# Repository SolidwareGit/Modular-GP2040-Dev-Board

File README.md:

# Modular-GP2040-Dev-Board
This is a development board for the RP2040 to enable creation of a modular GP2040-CE, using I2C, for fightsticks or other controller peripherals

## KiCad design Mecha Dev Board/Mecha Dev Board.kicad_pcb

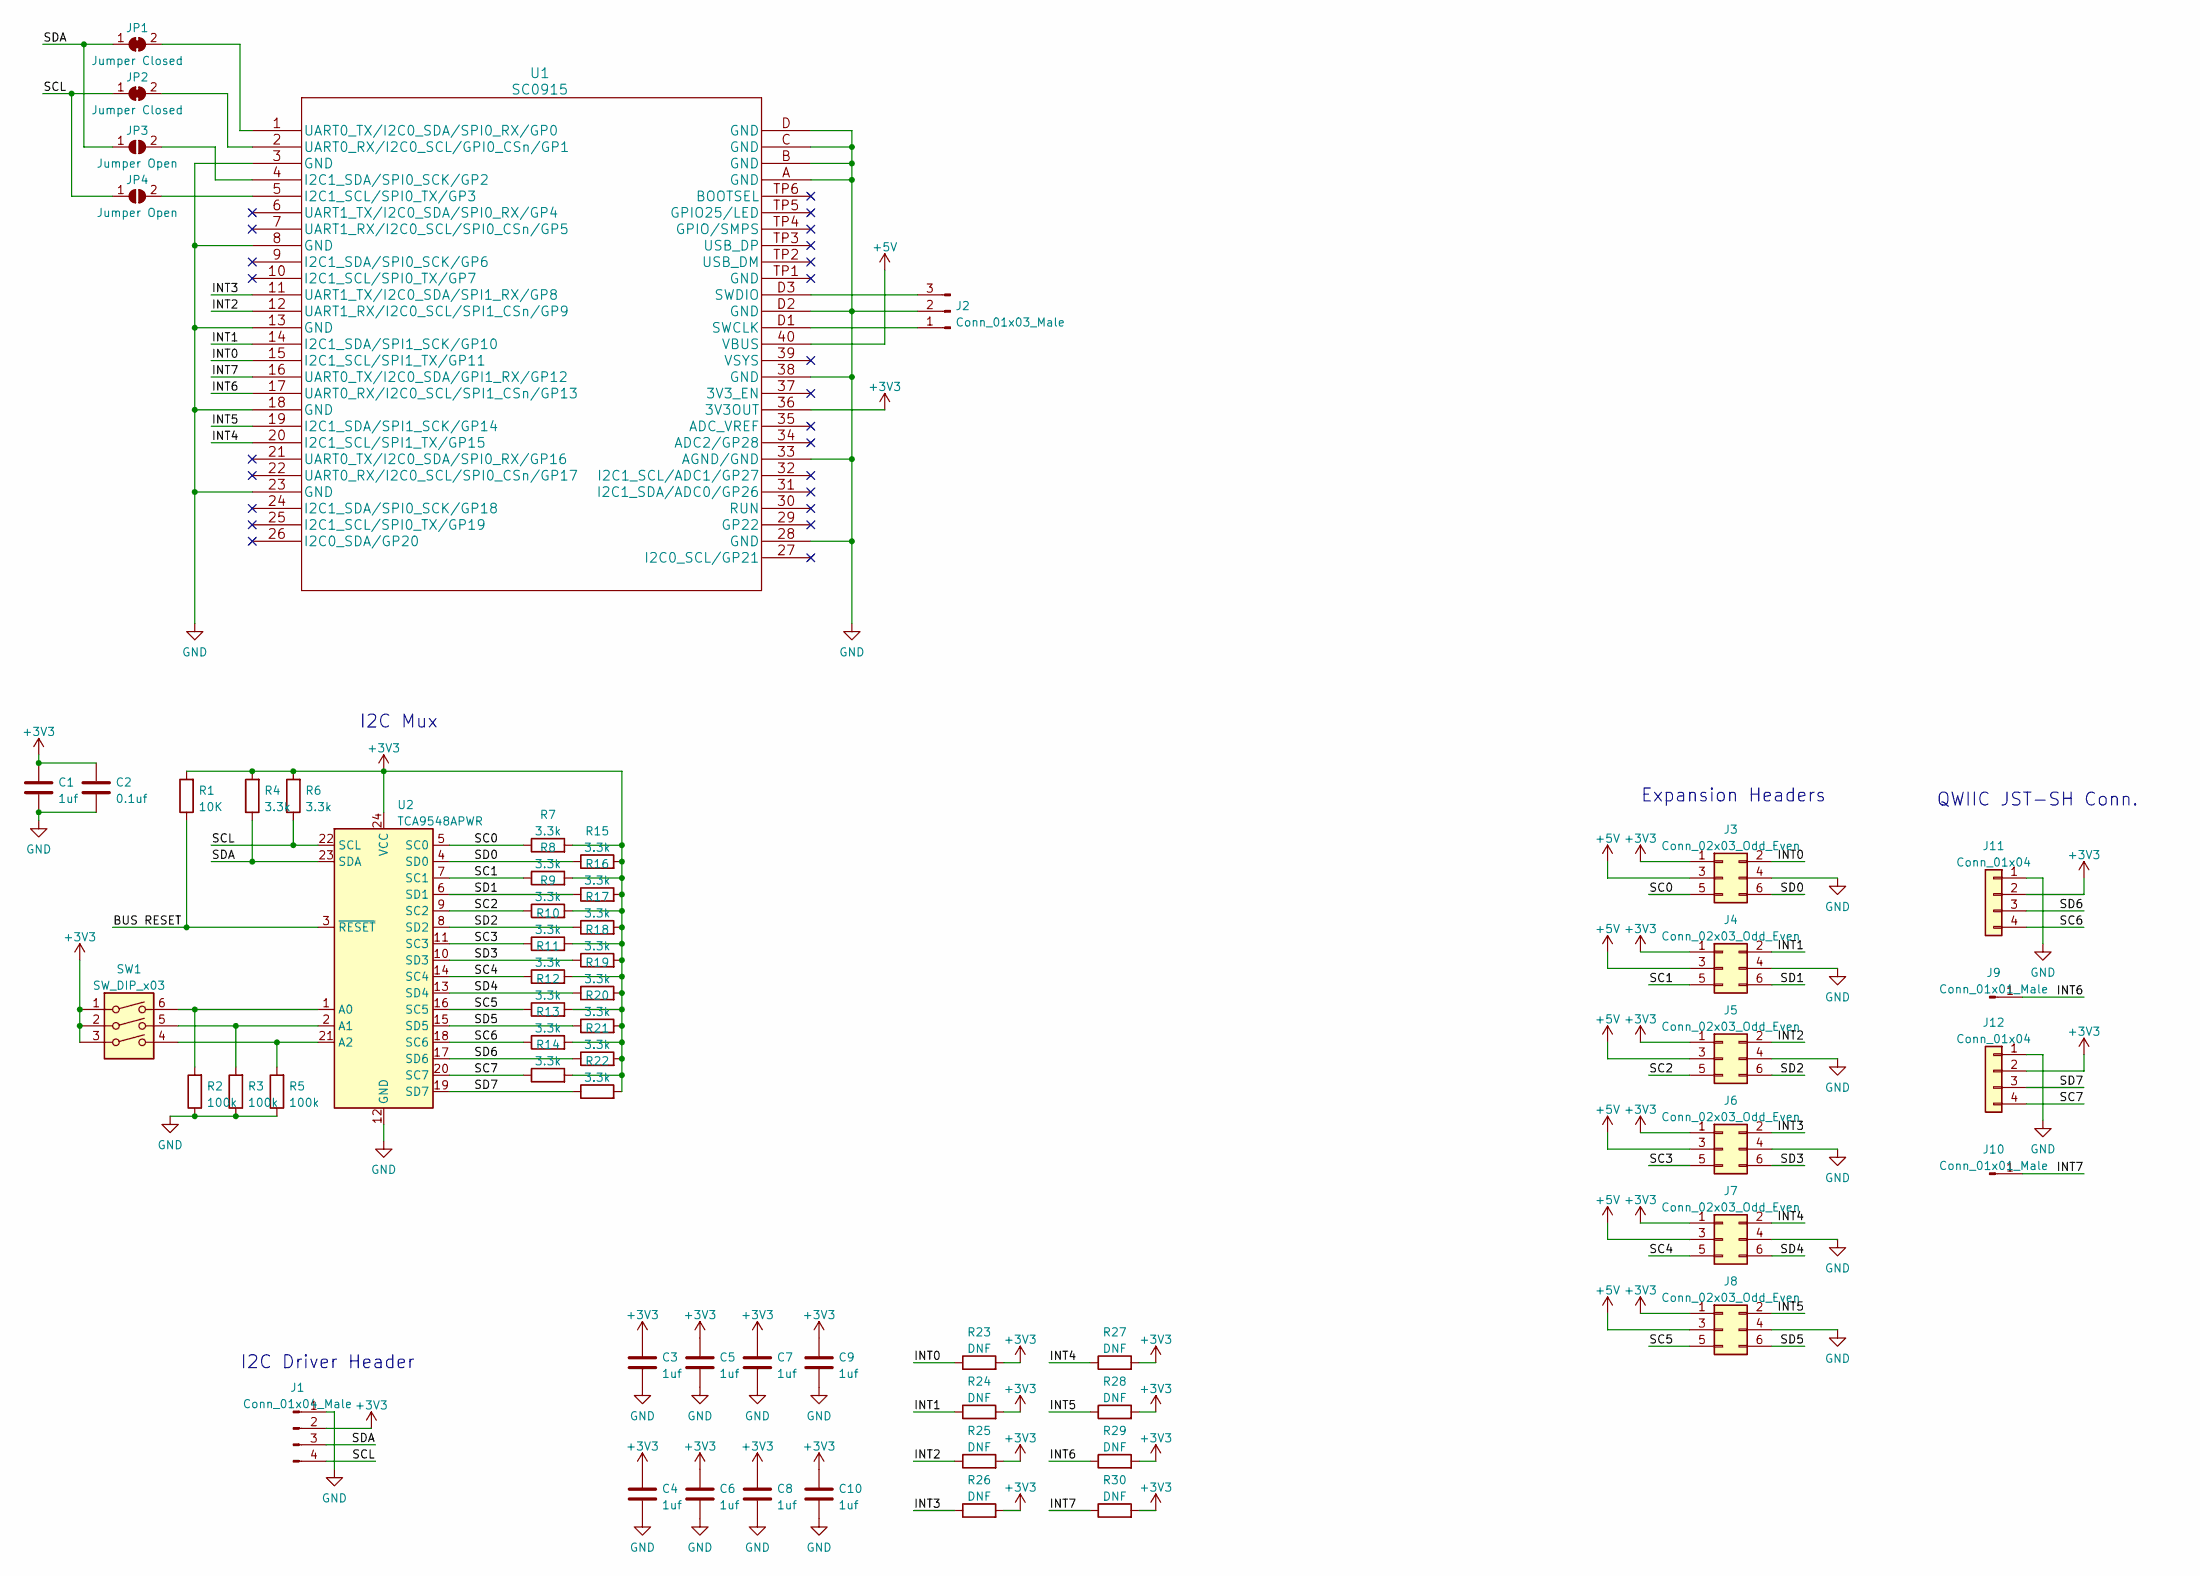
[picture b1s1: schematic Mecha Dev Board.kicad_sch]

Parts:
C1, C3, C4, C5, C6, C7, C8, C9, C10: 1uf; C_0805_2012Metric_Pad1.18x1.45mm_HandSolder
C2: 0.1uf; C_0805_2012Metric_Pad1.18x1.45mm_HandSolder
J1: Conn_01x04_Male; PinHeader_1x04_P2.54mm_Vertical
J2: Conn_01x03_Male; PinHeader_1x03_P2.54mm_Vertical
J3, J4, J5, J6, J7, J8: Conn_02x03_Odd_Even; PinHeader_2x03_P2.54mm_Vertical
J9, J10: Conn_01x01_Male; PinHeader_1x01_P2.54mm_Vertical
J11, J12: Conn_01x04; JST_SH_SM04B-SRSS-TB_1x04-1MP_P1.00mm_Horizontal
JP1, JP2: Jumper Closed; SolderJumper-2_P1.3mm_Bridged_Pad1.0x1.5mm
JP3, JP4: Jumper Open; SolderJumper-2_P1.3mm_Open_Pad1.0x1.5mm
R1: 10K; R_0805_2012Metric_Pad1.20x1.40mm_HandSolder
R2, R3, R5: 100k; R_0805_2012Metric_Pad1.20x1.40mm_HandSolder
R4, R6, R7, R8, R9, R10, R11, R12, R13, R14, R15, R16, R17, R18, R19, R20, R21, R22: 3.3k; R_0805_2012Metric_Pad1.20x1.40mm_HandSolder
R23, R24, R25, R26, R27, R28, R29, R30: DNF; R_0805_2012Metric_Pad1.20x1.40mm_HandSolder
SW1: SW_DIP_x03; SW_DIP_SPSTx03_Slide_6.7x9.18mm_W7.62mm_P2.54mm_LowProfile
U1: SC0915
U2: TCA9548APWR; TSSOP-24_4.4x7.8mm_P0.65mm

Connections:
+3V3: C1.2, C2.2, C3.2, C4.2, C5.2, C6.2, C7.2, C8.2, C9.2, C10.2, J1.2, J3.1, J4.1, J5.1, J6.1, J7.1, J8.1, J11.2, J12.2, R1.2, R4.2, R6.2, R7.2, R8.2, R9.2, R10.2, R11.2, R12.2, R13.2, R14.2, R15.2, R16.2, R17.2, R18.2, R19.2, R20.2, R21.2, R22.2, R23.2, R24.2, R25.2, R26.2, R27.2, R28.2, R29.2, R30.2, SW1.1, SW1.2, SW1.3, U1.36 (3V3OUT), U2.24 (VCC)
+5V: J3.3, J4.3, J5.3, J6.3, J7.3, J8.3, U1.40 (VBUS)
/BUS RESET: R1.1, U2.3 (~RESET)
/INT0: J3.2, R23.1, U1.15 (I2C1_SCL/SPI1_TX/GP11)
/INT1: J4.2, R24.1, U1.14 (I2C1_SDA/SPI1_SCK/GP10)
/INT2: J5.2, R25.1, U1.12 (UART1_RX/I2C0_SCL/SPI1_CSn/GP9)
/INT3: J6.2, R26.1, U1.11 (UART1_TX/I2C0_SDA/SPI1_RX/GP8)
/INT4: J7.2, R27.1, U1.20 (I2C1_SCL/SPI1_TX/GP15)
/INT5: J8.2, R28.1, U1.19 (I2C1_SDA/SPI1_SCK/GP14)
/INT6: J9.1, R29.1, U1.17 (UART0_RX/I2C0_SCL/SPI1_CSn/GP13)
/INT7: J10.1, R30.1, U1.16 (UART0_TX/I2C0_SDA/GPI1_RX/GP12)
/SC0: J3.5, R7.1, U2.5 (SC0)
/SC1: J4.5, R8.1, U2.7 (SC1)
/SC2: J5.5, R9.1, U2.9 (SC2)
/SC3: J6.5, R10.1, U2.11 (SC3)
/SC4: J7.5, R11.1, U2.14 (SC4)
/SC5: J8.5, R12.1, U2.16 (SC5)
/SC6: J11.4, R13.1, U2.18 (SC6)
/SC7: J12.4, R14.1, U2.20 (SC7)
/SCL: J1.4, JP2.1 (A), JP4.1 (A), R6.1, U2.22 (SCL)
/SD0: J3.6, R15.1, U2.4 (SD0)
/SD1: J4.6, R16.1, U2.6 (SD1)
/SD2: J5.6, R17.1, U2.8 (SD2)
/SD3: J6.6, R18.1, U2.10 (SD3)
/SD4: J7.6, R19.1, U2.13 (SD4)
/SD5: J8.6, R20.1, U2.15 (SD5)
/SD6: J11.3, R21.1, U2.17 (SD6)
/SD7: J12.3, R22.1, U2.19 (SD7)
/SDA: J1.3, JP1.1 (A), JP3.1 (A), R4.1, U2.23 (SDA)
GND: C1.1, C2.1, C3.1, C4.1, C5.1, C6.1, C7.1, C8.1, C9.1, C10.1, J1.1, J2.2, J3.4, J4.4, J5.4, J6.4, J7.4, J8.4, J11.1, J12.1, R2.1, R3.1, R5.1, U1.3 (GND), U1.8 (GND), U1.13 (GND), U1.18 (GND), U1.23 (GND), U1.28 (GND), U1.33 (AGND/GND), U1.38 (GND), U1.A (GND), U1.B (GND), U1.C (GND), U1.D (GND), U1.D2 (GND), U2.12 (GND)
unnamed: J2.1, U1.D1 (SWCLK)
unnamed: J2.3, U1.D3 (SWDIO)
unnamed: JP1.2 (B), U1.1 (UART0_TX/I2C0_SDA/SPI0_RX/GP0)
unnamed: JP2.2 (B), U1.2 (UART0_RX/I2C0_SCL/GPI0_CSn/GP1)
unnamed: JP3.2 (B), U1.4 (I2C1_SDA/SPI0_SCK/GP2)
unnamed: JP4.2 (B), U1.5 (I2C1_SCL/SPI0_TX/GP3)
unnamed: R2.2, SW1.6, U2.1 (A0)
unnamed: R3.2, SW1.5, U2.2 (A1)
unnamed: R5.2, SW1.4, U2.21 (A2)

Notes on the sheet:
I2C Driver Header
I2C Mux
Expansion Headers
QWIIC JST-SH Conn.

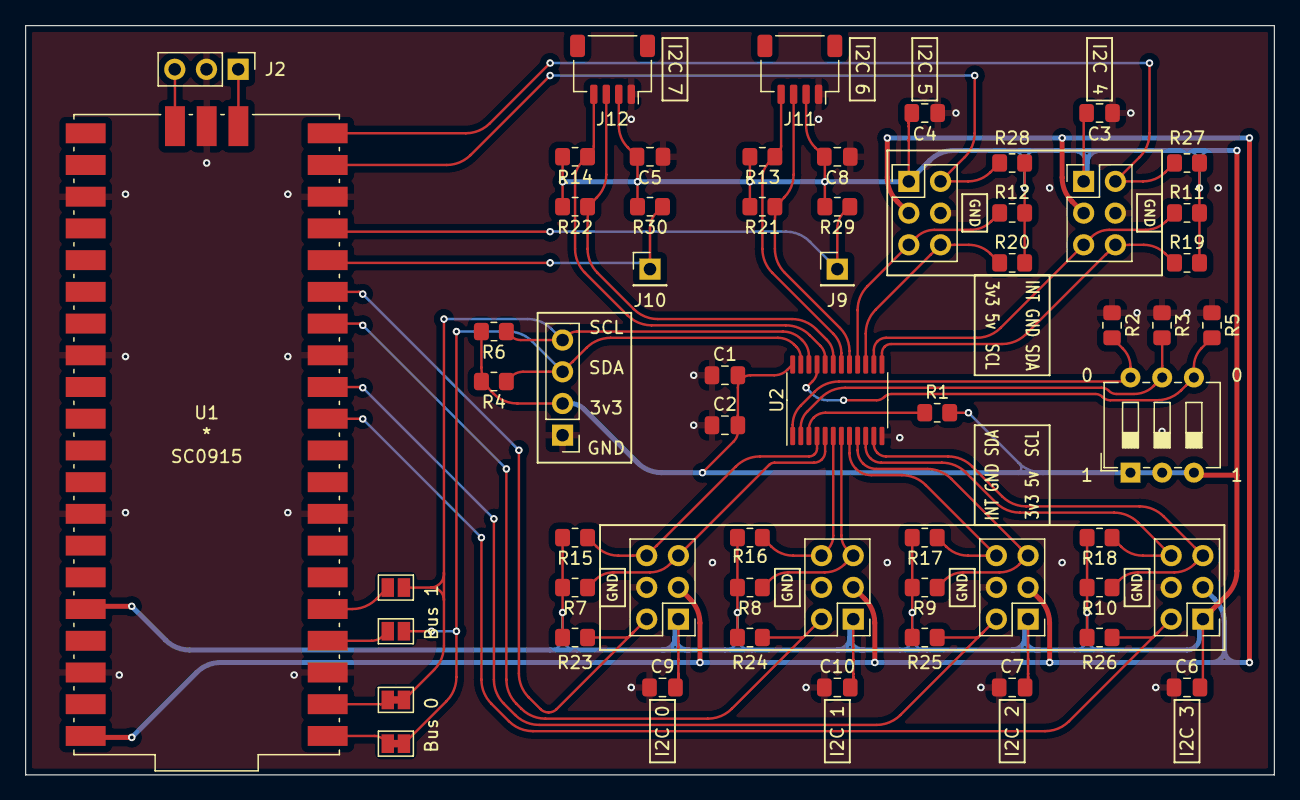
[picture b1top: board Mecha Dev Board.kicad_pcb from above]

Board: 2 copper layers, 100.0 x 60.0 mm, 59 parts (0 on the bottom side), 39 nets.

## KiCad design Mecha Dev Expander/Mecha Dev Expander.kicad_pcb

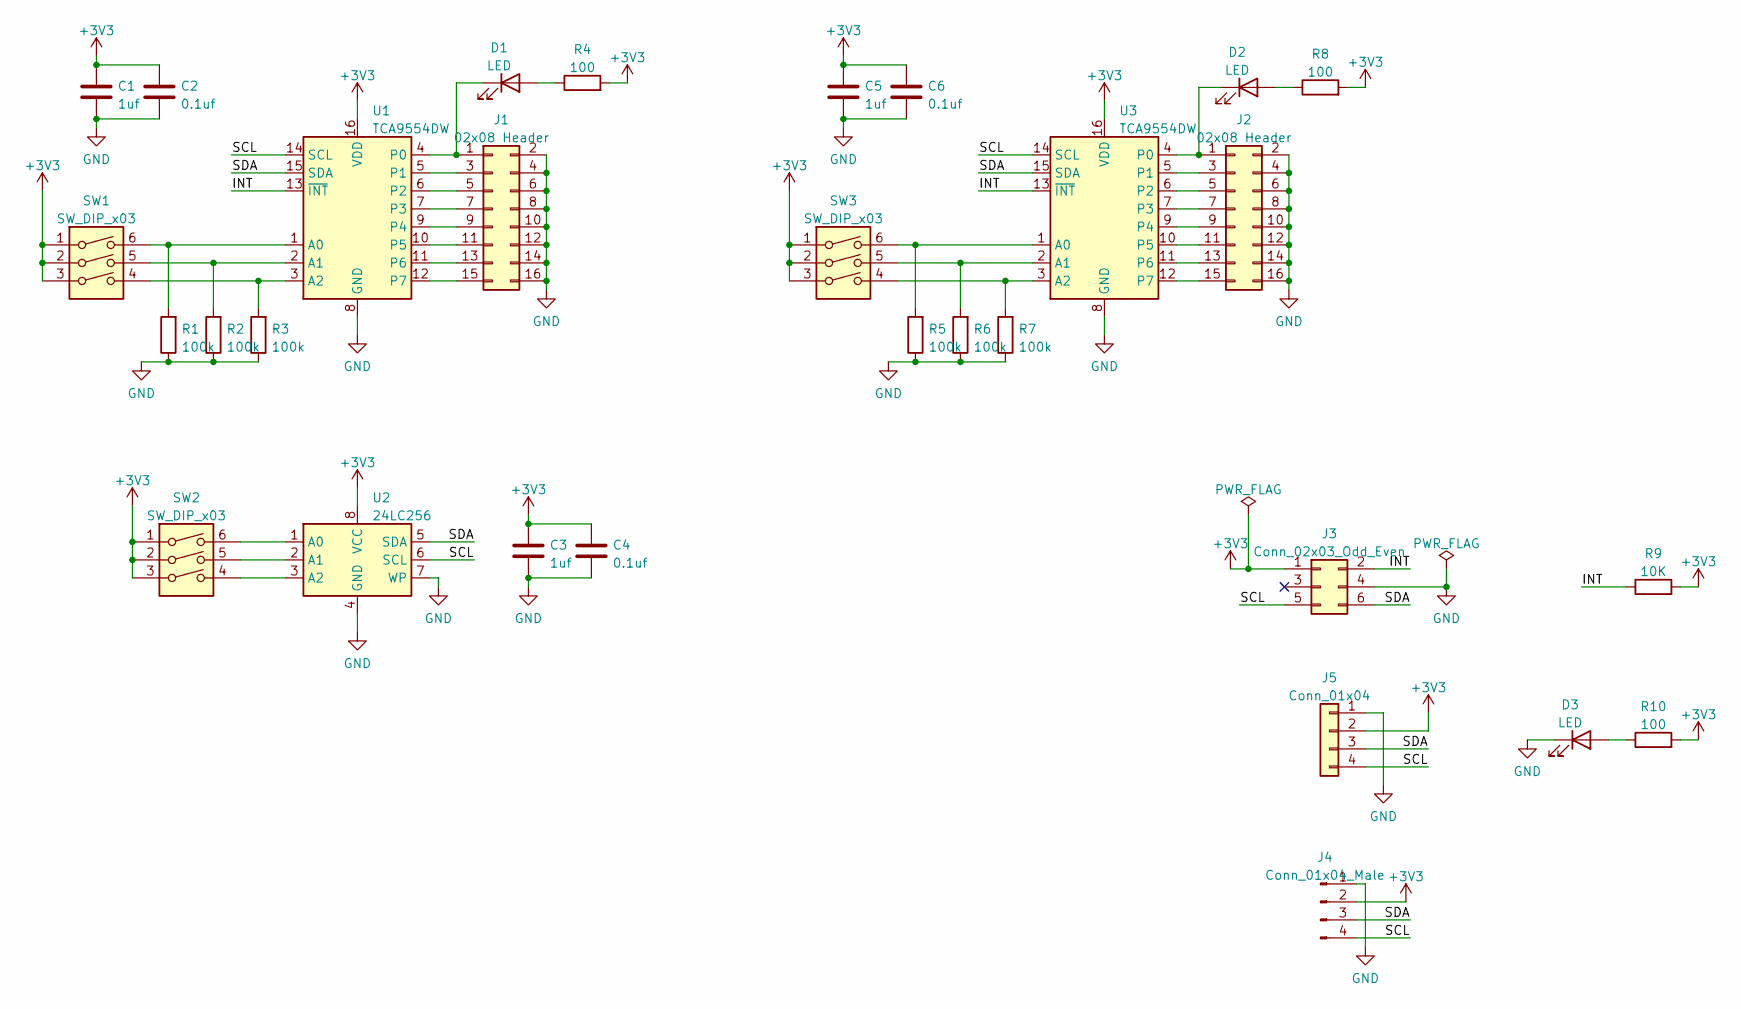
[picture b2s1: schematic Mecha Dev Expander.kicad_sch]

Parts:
C1, C3, C5: 1uf; C_0805_2012Metric_Pad1.18x1.45mm_HandSolder
C2, C4, C6: 0.1uf; C_0805_2012Metric_Pad1.18x1.45mm_HandSolder
D1, D2, D3: LED; LED_0805_2012Metric_Pad1.15x1.40mm_HandSolder
J1, J2: 02x08 Header; PinHeader_2x08_P2.54mm_Vertical
J3: Conn_02x03_Odd_Even; PinHeader_2x03_P2.54mm_Vertical
J4: Conn_01x04_Male; PinHeader_1x04_P2.54mm_Vertical
J5: Conn_01x04; JST_SH_SM04B-SRSS-TB_1x04-1MP_P1.00mm_Horizontal
R1, R2, R3, R5, R6, R7: 100k; R_0805_2012Metric_Pad1.20x1.40mm_HandSolder
R4, R8, R10: 100; R_0805_2012Metric_Pad1.20x1.40mm_HandSolder
R9: 10K; R_0805_2012Metric_Pad1.20x1.40mm_HandSolder
SW1, SW2, SW3: SW_DIP_x03; SW_DIP_SPSTx03_Slide_6.7x9.18mm_W7.62mm_P2.54mm_LowProfile
U1, U3: TCA9554DW; SOIC-16W_7.5x10.3mm_P1.27mm
U2: 24LC256; SOIC-8_3.9x4.9mm_P1.27mm

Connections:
+3V3: C1.2, C2.2, C3.2, C4.2, C5.2, C6.2, J3.1, J4.2, J5.2, R4.2, R8.2, R9.2, R10.2, SW1.1, SW1.2, SW1.3, SW2.1, SW2.2, SW2.3, SW3.1, SW3.2, SW3.3, U1.16 (VDD), U2.8 (VCC), U3.16 (VDD)
/INT: J3.2, R9.1, U1.13 (~INT), U3.13 (~INT)
/SCL: J3.5, J4.4, J5.4, U1.14 (SCL), U2.6 (SCL), U3.14 (SCL)
/SDA: J3.6, J4.3, J5.3, U1.15 (SDA), U2.5 (SDA), U3.15 (SDA)
GND: C1.1, C2.1, C3.1, C4.1, C5.1, C6.1, D3.1 (K), J1.2, J1.4, J1.6, J1.8, J1.10, J1.12, J1.14, J1.16, J2.2, J2.4, J2.6, J2.8, J2.10, J2.12, J2.14, J2.16, J3.4, J4.1, J5.1, R1.1, R2.1, R3.1, R5.1, R6.1, R7.1, U1.8 (GND), U2.4 (GND), U2.7 (WP), U3.8 (GND)
unnamed: D1.1 (K), J1.1, U1.4 (P0)
unnamed: D1.2 (A), R4.1
unnamed: D2.1 (K), J2.1, U3.4 (P0)
unnamed: D2.2 (A), R8.1
unnamed: D3.2 (A), R10.1
unnamed: J1.3, U1.5 (P1)
unnamed: J1.5, U1.6 (P2)
unnamed: J1.7, U1.7 (P3)
unnamed: J1.9, U1.9 (P4)
unnamed: J1.11, U1.10 (P5)
unnamed: J1.13, U1.11 (P6)
unnamed: J1.15, U1.12 (P7)
unnamed: J2.3, U3.5 (P1)
unnamed: J2.5, U3.6 (P2)
unnamed: J2.7, U3.7 (P3)
unnamed: J2.9, U3.9 (P4)
unnamed: J2.11, U3.10 (P5)
unnamed: J2.13, U3.11 (P6)
unnamed: J2.15, U3.12 (P7)
unnamed: R1.2, SW1.6, U1.1 (A0)
unnamed: R2.2, SW1.5, U1.2 (A1)
unnamed: R3.2, SW1.4, U1.3 (A2)
unnamed: R5.2, SW3.6, U3.1 (A0)
unnamed: R6.2, SW3.5, U3.2 (A1)
unnamed: R7.2, SW3.4, U3.3 (A2)
unnamed: SW2.4, U2.3 (A2)
unnamed: SW2.5, U2.2 (A1)
unnamed: SW2.6, U2.1 (A0)

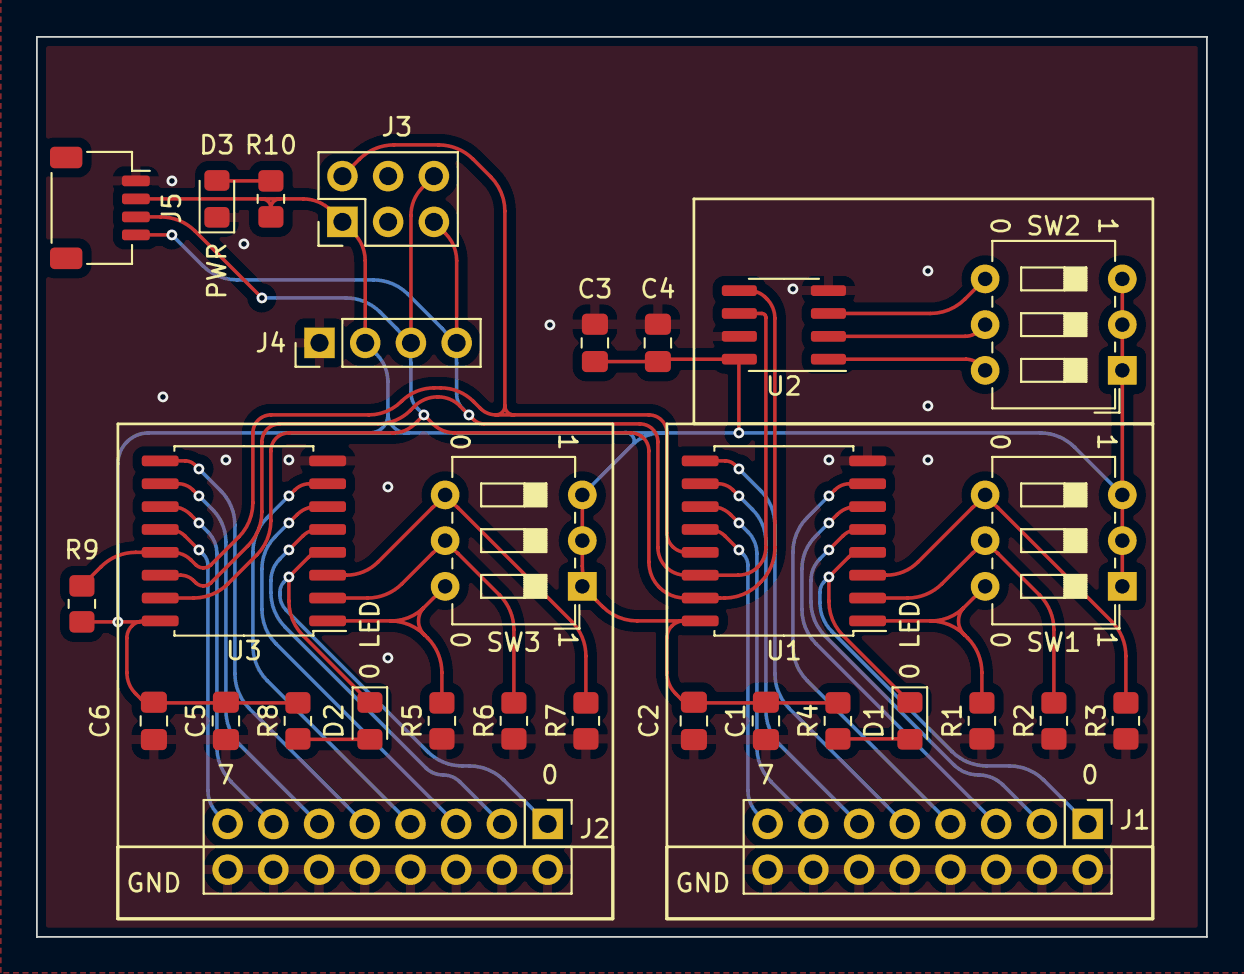
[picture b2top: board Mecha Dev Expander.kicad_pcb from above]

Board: 2 copper layers, 65.0 x 50.0 mm, 30 parts (0 on the bottom side), 33 nets.

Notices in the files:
parts and their libraries:
Copyright 2021 Accelerated Designs. All rights reserved.
